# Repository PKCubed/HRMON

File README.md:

# HRMON
A Stethoscope-shaped Heart Rate Monitor Badge<br>
Created for WWU ENGR355 Winter 2026<br>
Based on the NXP Kinetis KL25 MCU

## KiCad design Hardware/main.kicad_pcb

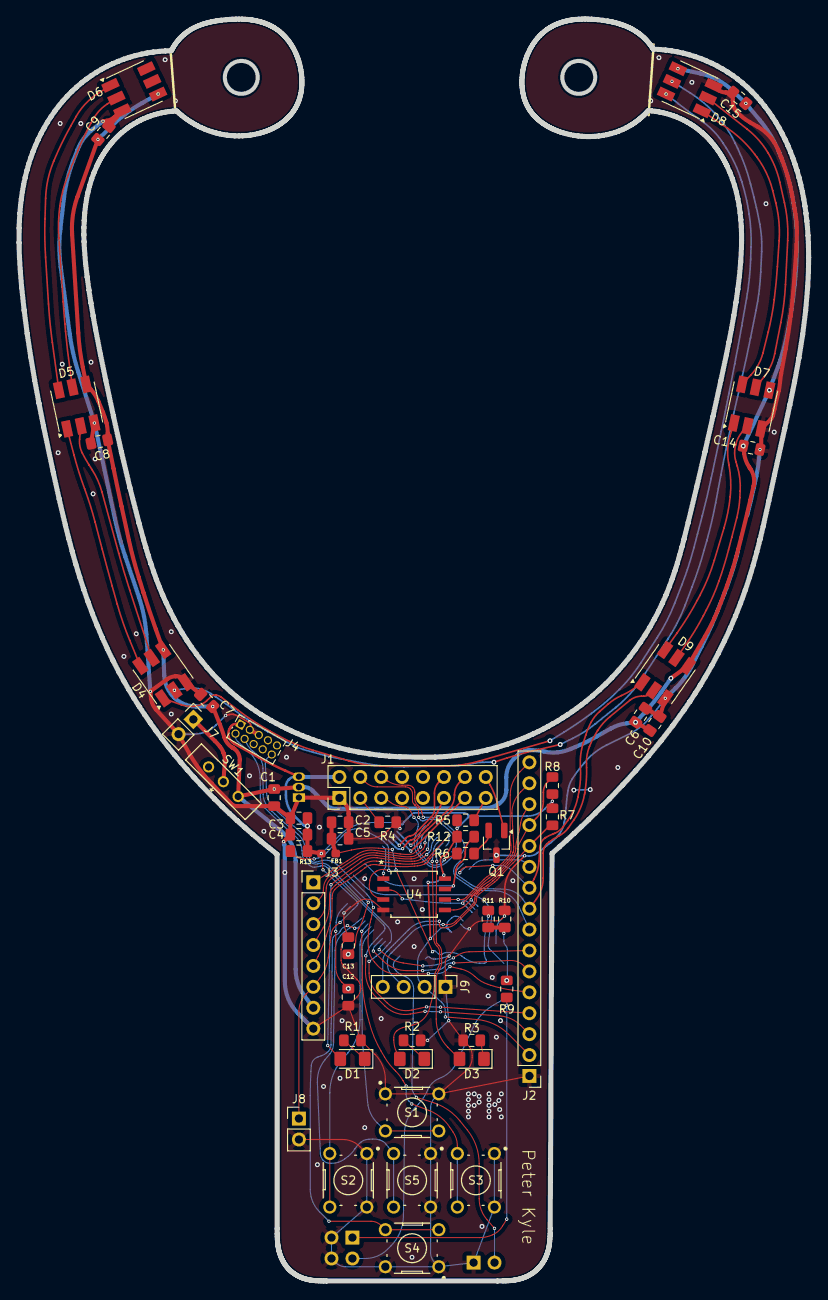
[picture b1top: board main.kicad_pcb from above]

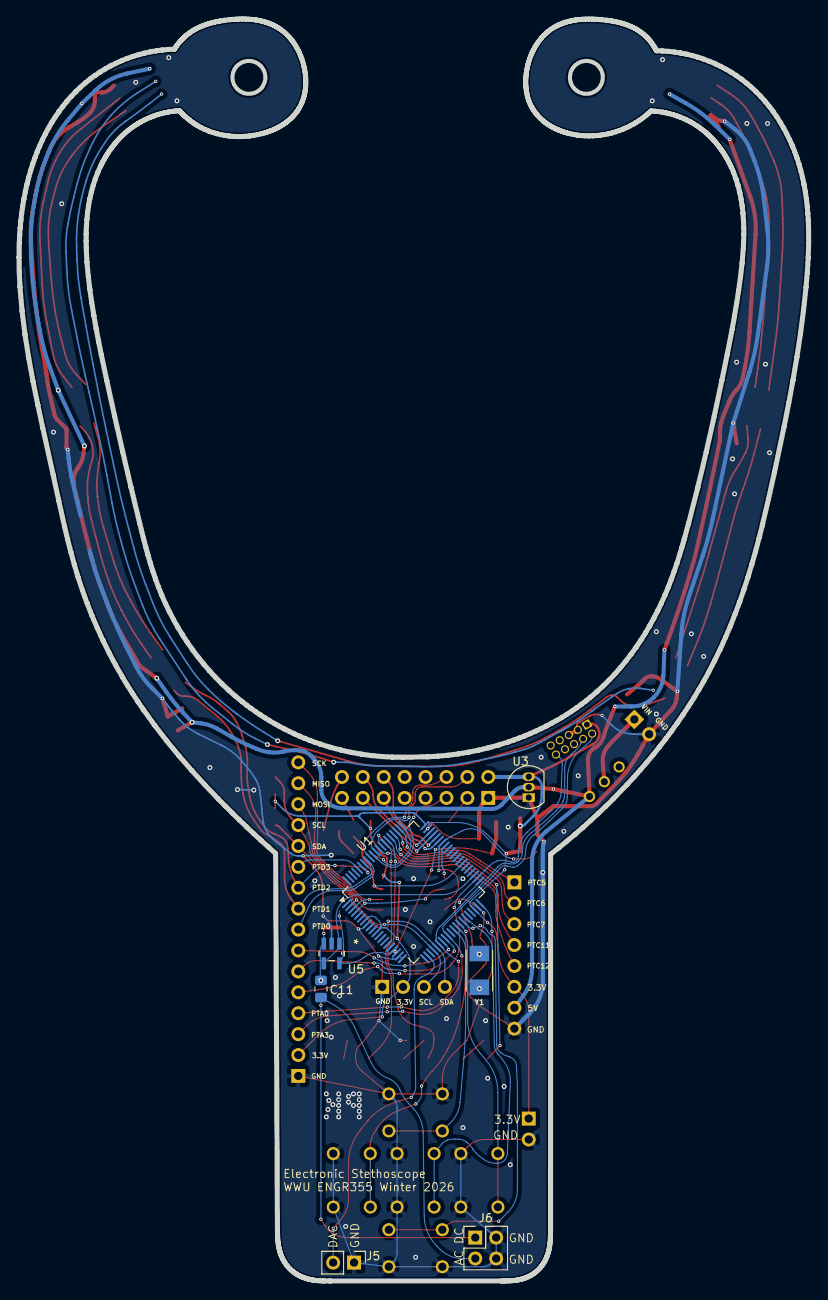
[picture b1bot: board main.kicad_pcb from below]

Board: 2 copper layers, 95.9 x 153.3 mm, 59 parts (7 on the bottom side), 67 nets.

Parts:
C1, C3, C12, C13: 10uF; C_0805_2012Metric_Pad1.18x1.45mm_HandSolder
C2, C6: 1uF; C_0805_2012Metric_Pad1.18x1.45mm_HandSolder
C4, C5, C7, C8, C9, C10, C14, C15: 0.1uF; C_0805_2012Metric_Pad1.18x1.45mm_HandSolder
C11: 1u; C_0805_2012Metric_Pad1.18x1.45mm_HandSolder
D1, D2, D3: LED; LED_1206_3216Metric_Pad1.42x1.75mm_HandSolder
D4, D5, D6, D7, D8, D9: APA102; LED_RGB_5050-6
FB1: FerriteBead; L_0603_1608Metric_Pad1.05x0.95mm_HandSolder
J1: 8x2 Character LCD; PinHeader_2x08_P2.54mm_Vertical
J2: Conn_01x16_Pin; PinHeader_1x16_P2.54mm_Vertical
J3: Conn_01x08_Pin; PinHeader_1x08_P2.54mm_Vertical
J4: Conn_02x05_Odd_Even; PinSocket_2x05_P1.27mm_Vertical
J5, J7, J8: Conn_01x02_Pin; PinHeader_1x02_P2.54mm_Vertical
J6: Conn_02x02_Odd_Even; PinHeader_2x02_P2.54mm_Vertical
J9: Conn_01x04_Pin; PinHeader_1x04_P2.54mm_Vertical
Q1: NPN; SOT-23_Handsoldering
R1, R2, R3: 220; C_0805_2012Metric_Pad1.18x1.45mm_HandSolder
R4, R5: 510; C_0805_2012Metric_Pad1.18x1.45mm_HandSolder
R6: 1k; C_0805_2012Metric_Pad1.18x1.45mm_HandSolder
R7, R8: 4.7k; C_0805_2012Metric_Pad1.18x1.45mm_HandSolder
R9: 1000R; C_0805_2012Metric_Pad1.18x1.45mm_HandSolder
R10, R11: 2Meg; C_0805_2012Metric_Pad1.18x1.45mm_HandSolder
R12, R13: 10k; C_0805_2012Metric_Pad1.18x1.45mm_HandSolder
S1, S2, S3, S4, S5: B3F-1000; SW_B3F-1000
SW1: 09.03290.01; 09.03290_EAO
U1: MKL25Z128VLK4; LQFP-80_12x12mm_P0.5mm
U3: MCP1700x-330xxTO; TO-92_Inline
U4: 25LC1024-I/SM; SOIJ8-M_MC_MCH
U5: OPA377AIDBVR; DBV5
Y1: ABM3-8.000MHZ-D2Y-T; XTAL_ABM3-8.000MHZ-D2Y-T

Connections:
+3.3V: C3.1, C4.1, FB1.1, J1.2, J2.2, J3.6, J4.1, J8.1, J9.2, R5.1, R7.2, R8.1, R12.2, R13.2, U1.7 (VDD), U1.11 (VOUT33), U1.38 (VDD), U1.60 (VDD), U3.3 (VO), U4.8 (VCC)
+3.3V_A: C2.1, C5.1, FB1.2, R11.1, U1.17 (VDDA), U1.18 (VREFH), U5.5 (V+)
+5V: C1.1, C6.1, C7.1, C8.1, C9.1, C10.1, C14.1, C15.1, D4.4 (VCC), D5.4 (VCC), D6.4 (VCC), D7.4 (VCC), D8.4 (VCC), D9.4 (VCC), J3.7, SW1.2, U3.2 (VI)
EEPROM_CS: U1.53 (PTB18), U4.1 (*CS)
EEPROM_HOLD: R12.1, U1.47 (PTB8), U4.7 (*HOLD)
EEPROM_SCK: J2.16, U1.3 (PTE2), U4.6 (SCK)
EEPROM_SI: J2.14, U1.2 (PTE1), U4.5 (SI)
EEPROM_SO: J2.15, U1.4 (PTE3), U4.2 (SO)
EEPROM_WP: R13.1, U1.54 (PTB19), U4.3 (*WP)
EXTAL0: C12.1, U1.40 (PTA18), Y1.1
GND: C1.2, C2.2, C3.2, C4.2, C5.2, C6.2, C7.2, C8.2, C9.2, C10.2, C12.2, C13.2, C14.2, C15.2, D4.3 (GND), D5.3 (GND), D6.3 (GND), D7.3 (GND), D8.3 (GND), D9.3 (GND), J1.1, J2.1, J3.8, J4.3, J4.5, J5.1, J6.2, J6.4, J7.2, J8.2, J9.1, Q1.3 (E), R1.2, R2.2, R3.2, R4.1, R10.2, S1.1, S1.2, S2.1, S2.2, S3.1, S3.2, S4.1, S4.2, S5.1, S5.2, U1.8 (VSS), U1.19 (VREFL), U1.20 (VSSA), U1.39 (VSS), U1.59 (VSS), U3.1 (GND), U4.4 (VSS), U5.2 (V-)
I2C_SCL: J2.13, J9.3, R8.2, U1.24 (PTE24)
I2C_SDA: J2.12, J9.4, R7.1, U1.25 (PTE25)
LCD_BL: R6.1, U1.61 (PTC4/LLWU_P8)
LCD_DB4: J1.11, U1.55 (PTC0)
LCD_DB5: J1.12, U1.56 (PTC1/LLWU_P6/RTC_CLKIN)
LCD_DB6: J1.13, U1.57 (PTC2)
LCD_DB7: J1.14, U1.58 (PTC3/LLWU_P7)
LCD_EN: J1.6, U1.72 (PTC17)
LCD_RS: J1.4, U1.70 (PTC13)
LCD_RW: J1.5, U1.71 (PTC16)
unnamed: D1.1 (K), R1.1
unnamed: D2.1 (K), R2.1
unnamed: D3.1 (K), R3.1
unnamed: D4.2 (CI), D8.5 (CO)
unnamed: D4.5 (CO), D5.2 (CI)
unnamed: D4.1 (DI), D8.6 (DO)
unnamed: D4.6 (DO), D5.1 (DI)
unnamed: D5.5 (CO), D6.2 (CI)
unnamed: D5.6 (DO), D6.1 (DI)
unnamed: D7.2 (CI), D9.5 (CO)
unnamed: D7.5 (CO), D8.2 (CI)
unnamed: D7.1 (DI), D9.6 (DO)
unnamed: D7.6 (DO), D8.1 (DI)
unnamed: J1.3, R4.2
unnamed: J1.15, R5.2
unnamed: J1.16, Q1.1 (C)
unnamed: J6.1, R9.1
unnamed: C11.2, J6.3
unnamed: J7.1, SW1.1
unnamed: Q1.2 (B), R6.2
unnamed: C11.1, R9.2, R10.1, R11.2, U5.3 (IN+)
Opamp_Out: U1.43 (PTB0/LLWU_P5), U5.1 (OUT), U5.4 (IN-)
PTA0: J2.4, J4.4, U1.26 (PTA0)
PTA1: J2.7, U1.27 (PTA1)
PTA2: J2.6, U1.28 (PTA2)
PTA3: J2.3, J4.2, U1.29 (PTA3)
PTA5: S1.3, S1.4, U1.31 (PTA5)
PTA12: S2.3, S2.4, U1.32 (PTA12)
PTA13: S3.3, S3.4, U1.33 (PTA13)
PTA14: S4.3, S4.4, U1.34 (PTA14)
PTA15: S5.3, S5.4, U1.35 (PTA15)
PTA20: J2.5, J4.10, U1.42 (PTA20)
PTC5: J3.1, U1.62 (PTC5/LLWU_P9)
PTC6: J3.2, U1.63 (PTC6/LLWU_P10)
PTC7: J3.3, U1.64 (PTC7)
PTC8: D1.2 (A), U1.65 (PTC8)
PTC9: D2.2 (A), U1.66 (PTC9)
PTC10: D3.2 (A), U1.67 (PTC10)
PTC11: J3.4, U1.68 (PTC11)
PTC12: J3.5, U1.69 (PTC12)
PTD0: J2.8, U1.73 (PTD0)
PTD1: D9.2 (CI), J2.9, U1.74 (PTD1)
PTD2: D9.1 (DI), J2.10, U1.75 (PTD2)
PTD3: J2.11, U1.76 (PTD3)
PTE30: J5.2, U1.22 (PTE30)
XTAL0: C13.1, U1.41 (PTA19), Y1.2

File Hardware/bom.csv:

"Id";"Designator";"Footprint";"Quantity";"Designation";"Supplier and ref";
1;"C3,C1,C12,C13";"C_0805_2012Metric_Pad1.18x1.45mm_HandSolder";4;"10uF";;;
2;"C14,C4,C5,C10,C15,C9,C7,C8";"C_0805_2012Metric_Pad1.18x1.45mm_HandSolder";8;"0.1uF";;;
3;"J3";"PinHeader_1x08_P2.54mm_Vertical";1;"Conn_01x08_Pin";;;
4;"D1,D2,D3";"LED_1206_3216Metric_Pad1.42x1.75mm_HandSolder";3;"LED";;;
5;"J9";"PinHeader_1x04_P2.54mm_Vertical";1;"Conn_01x04_Pin";;;
6;"D5,D7,D6,D8,D9,D4";"LED_RGB_5050-6";6;"APA102";;;
7;"R2,R1,R3";"C_0805_2012Metric_Pad1.18x1.45mm_HandSolder";3;"220";;;
8;"S1,S2,S5,S3,S4";"SW_B3F-1000";5;"B3F-1000";;;
9;"R13,R12";"C_0805_2012Metric_Pad1.18x1.45mm_HandSolder";2;"10k";;;
10;"R5,R4";"C_0805_2012Metric_Pad1.18x1.45mm_HandSolder";2;"510";;;
11;"C2,C6";"C_0805_2012Metric_Pad1.18x1.45mm_HandSolder";2;"1uF";;;
12;"U4";"SOIJ8-M_MC_MCH";1;"25LC1024-I/SM";;;
13;"R8,R7";"C_0805_2012Metric_Pad1.18x1.45mm_HandSolder";2;"4.7k";;;
14;"R6";"C_0805_2012Metric_Pad1.18x1.45mm_HandSolder";1;"1k";;;
15;"R11,R10";"C_0805_2012Metric_Pad1.18x1.45mm_HandSolder";2;"2Meg";;;
16;"FB1";"L_0603_1608Metric_Pad1.05x0.95mm_HandSolder";1;"FerriteBead";;;
17;"J1";"PinHeader_2x08_P2.54mm_Vertical";1;"8x2 Character LCD";;;
18;"R9";"C_0805_2012Metric_Pad1.18x1.45mm_HandSolder";1;"1000R";;;
19;"J8,J7,J5";"PinHeader_1x02_P2.54mm_Vertical";3;"Conn_01x02_Pin";;;
20;"J2";"PinHeader_1x16_P2.54mm_Vertical";1;"Conn_01x16_Pin";;;
21;"J4";"PinSocket_2x05_P1.27mm_Vertical";1;"Conn_02x05_Odd_Even";;;
22;"SW1";"09.03290_EAO";1;"09.03290.01";;;
23;"Q1";"SOT-23_Handsoldering";1;"NPN";;;
24;"C11";"C_0805_2012Metric_Pad1.18x1.45mm_HandSolder";1;"1u";;;
25;"Y1";"XTAL_ABM3-8.000MHZ-D2Y-T";1;"ABM3-8.000MHZ-D2Y-T";;;
26;"U1";"LQFP-80_12x12mm_P0.5mm";1;"MKL25Z128VLK4";;;
27;"U5";"DBV5";1;"OPA377AIDBVR";;;
28;"J6";"PinHeader_2x02_P2.54mm_Vertical";1;"Conn_02x02_Odd_Even";;;
29;"U3";"TO-92_Inline";1;"MCP1700x-330xxTO";;;

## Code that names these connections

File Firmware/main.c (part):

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#define MASK(x) (1UL << (x))

// Pin Definitions
#define LCD_EN 17 // PTC17 LCD Enable (Clock)
#define LCD_RW 16 // PTC16 LCD Read/Write
#define LCD_RS 13 // PTC13 LCD Register Select

// LCD Data pins are PTC0-PTC3

#define LCD_BL 4 // PTC4 Backlight


// Buttons
#define BUTTON_UP 5 // PTA5
#define BUTTON_LEFT 12 // PTA12
#define BUTTON_RIGHT 13 // PTA13
#define BUTTON_DOWN 14 // PTA14
#define BUTTON_CENTER 15 // PTA15

#define DEBOUNCE_DURATION 2000000ULL // Clock Cycles

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
void LED_init() {
	PWM_init();
	PORTC->PCR[10] = PORT_PCR_MUX(1); // Setup green led (PTC10) as GPIO
	PTC->PDDR |= (1 << 10); // Setup green led (PTC10) as output
	PTC->PCOR = (1 << 10); // Turn off green led
}
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
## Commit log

2026-03-06 Correct spelling and capitalization in README
2026-03-08 Fully functioning BPM measurement and LED effects added
    Other than the measurement, menu options have no functionality yet.
2026-03-08 Revise title and include project image in README
    Updated project title and added an image.
2026-03-08 Update README with project details and MCU info
    Added project creation details and MCU information.
2026-03-08 Update README with project information and image
    Added project details and image to README
2026-03-08 Update README formatting and remove extra lines
2026-03-08 Add second image to README
    Added a second image to the README file.
2026-03-08 Fixed LCD Bug in Measurement Mode
    When the LCD prints a 3 digit number, then goes back to -- because the pulse period was too long, it didn't lead with a space, so the first digit of the 3 digit number was left. This has been fixed n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
2026-03-09 Finished Implementing Credits and Reset
    Also fixed 2025 to 2026 in the credits_text
2026-03-11 Changed LCD backlight resistance to 0
2026-03-15 Fixed Test Page LEDs and Reset
2026-03-15 Added 3 standard LEDs to the test mode
2026-03-15 Included class title in credits string
2026-03-15 Implemented slow RGB rainbow effect during credit's screen
2026-03-15 Implemented fade in on credits RGB rainbow effect
